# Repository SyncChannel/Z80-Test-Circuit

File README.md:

# Z80-Test-Circuit
https://oshpark.com/projects/BlrcG0fj

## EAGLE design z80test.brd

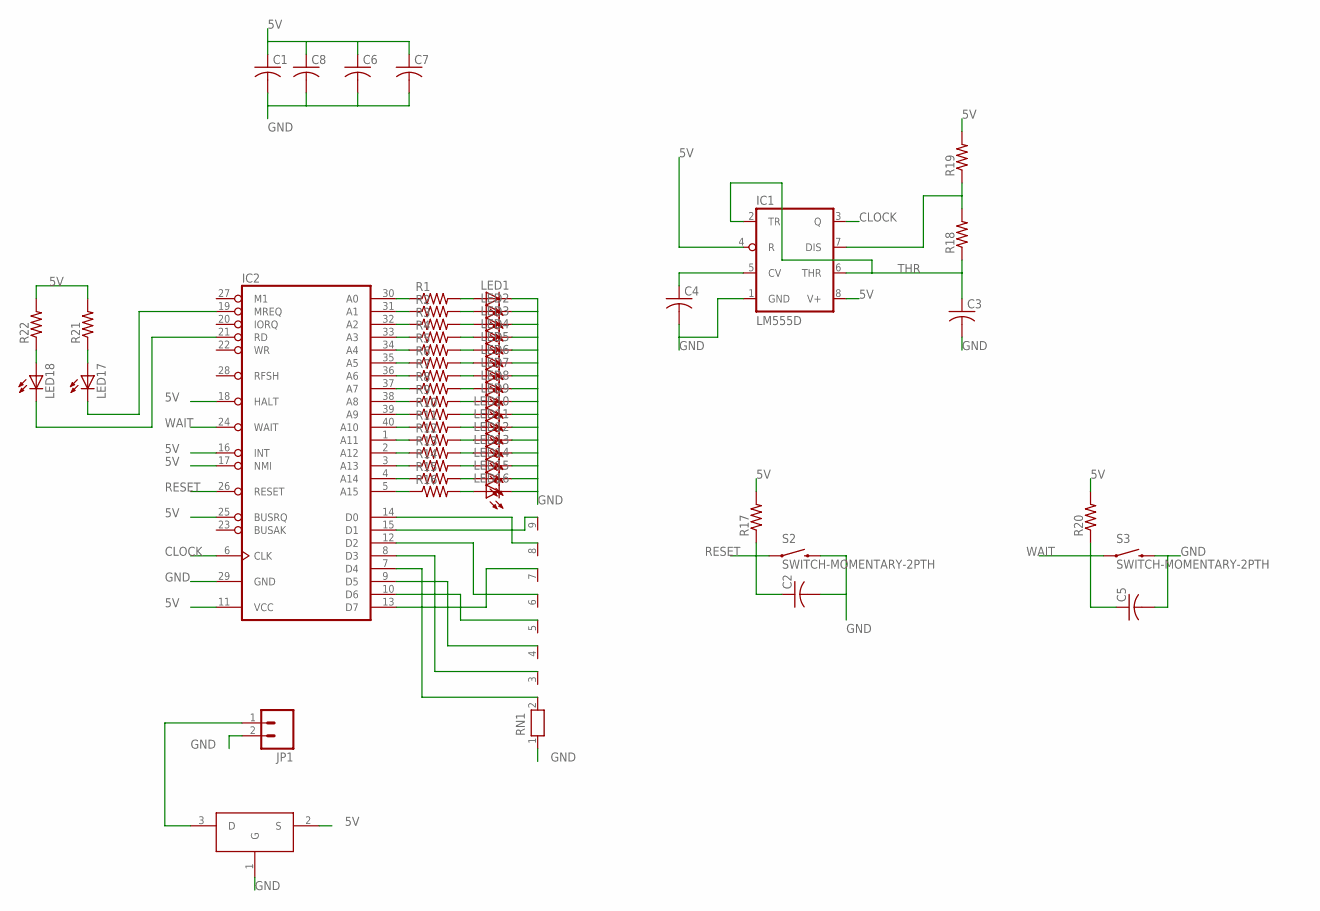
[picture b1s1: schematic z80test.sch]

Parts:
C1: C-USC0805K; C0805K
C2, C3, C4, C5, C6, C7, C8: C-USC0603; C0603
IC1: LM555D; SO08
IC2: Z80CPU; DIL40
JP1: M02PTH; 1X02
LED1, LED2, LED3, LED4, LED5, LED6, LED7, LED8, LED9, LED10, LED11, LED12, LED13, LED14, LED15, LED16, LED17, LED18: LEDCHIPLED_0805; CHIPLED_0805
R1, R2, R3, R4, R5, R6, R7, R8, R9, R10, R11, R12, R13, R14, R15, R16, R17, R18, R19, R20, R21, R22: R-US_R0603; R0603
RN1: RN08; RN-9
S2, S3: SWITCH-MOMENTARY-2PTH; TACTILE-PTH
U$1: PMOS_RP; SOT23-3

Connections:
5V: C1.1, C6.1, C7.1, C8.1, IC1.4 (R), IC1.8 (V+), IC2.11 (VCC), IC2.16 (INT), IC2.17 (NMI), IC2.18 (HALT), IC2.25 (BUSRQ), R17.2, R19.2, R20.2, R21.2, R22.2, U$1.2 (S)
CLOCK: IC1.3 (Q), IC2.6 (CLK)
GND: C1.2, C2.2, C3.2, C4.2, C5.2, C6.2, C7.2, C8.2, IC1.1 (GND), IC2.29 (GND), JP1.2, LED1.C, LED2.C, LED3.C, LED4.C, LED5.C, LED6.C, LED7.C, LED8.C, LED9.C, LED10.C, LED11.C, LED12.C, LED13.C, LED14.C, LED15.C, LED16.C, RN1.1, S2.3 (2), S3.3 (2), U$1.1 (G)
JUNCTION: IC1.7 (DIS), R18.2, R19.1
unnamed: IC2.15 (D1), RN1.9
unnamed: IC2.14 (D0), RN1.8
unnamed: IC2.13 (D7), RN1.7
unnamed: IC2.12 (D2), RN1.6
unnamed: IC2.10 (D6), RN1.5
unnamed: IC2.9 (D5), RN1.4
unnamed: IC2.8 (D3), RN1.3
unnamed: IC2.7 (D4), RN1.2
unnamed: IC2.30 (A0), R1.1
unnamed: IC2.31 (A1), R2.1
unnamed: IC2.32 (A2), R3.1
unnamed: IC2.33 (A3), R4.1
unnamed: IC2.34 (A4), R5.1
unnamed: IC2.35 (A5), R6.1
unnamed: IC2.36 (A6), R7.1
unnamed: IC2.37 (A7), R8.1
unnamed: IC2.38 (A8), R9.1
unnamed: IC2.39 (A9), R10.1
unnamed: IC2.40 (A10), R11.1
unnamed: IC2.1 (A11), R12.1
unnamed: IC2.2 (A12), R13.1
unnamed: IC2.3 (A13), R14.1
unnamed: IC2.4 (A14), R15.1
unnamed: IC2.5 (A15), R16.1
unnamed: LED1.A, R1.2
unnamed: LED2.A, R2.2
unnamed: LED3.A, R3.2
unnamed: LED4.A, R4.2
unnamed: LED5.A, R5.2
unnamed: LED6.A, R6.2
unnamed: LED7.A, R7.2
unnamed: LED8.A, R8.2
unnamed: LED9.A, R9.2
unnamed: LED10.A, R10.2
unnamed: LED11.A, R11.2
unnamed: LED12.A, R12.2
unnamed: LED13.A, R13.2
unnamed: LED14.A, R14.2
unnamed: LED15.A, R15.2
unnamed: LED16.A, R16.2
unnamed: C4.1, IC1.5 (CV)
unnamed: JP1.1, U$1.3 (D)
unnamed: LED17.A, R21.1
unnamed: LED18.A, R22.1
unnamed: IC2.19 (MREQ), LED17.C
unnamed: IC2.21 (RD), LED18.C
RESET: C2.1, IC2.26 (RESET), R17.1, S2.1
THR: C3.1, IC1.2 (TR), IC1.6 (THR), R18.1
WAIT: C5.1, IC2.24 (WAIT), R20.1, S3.1

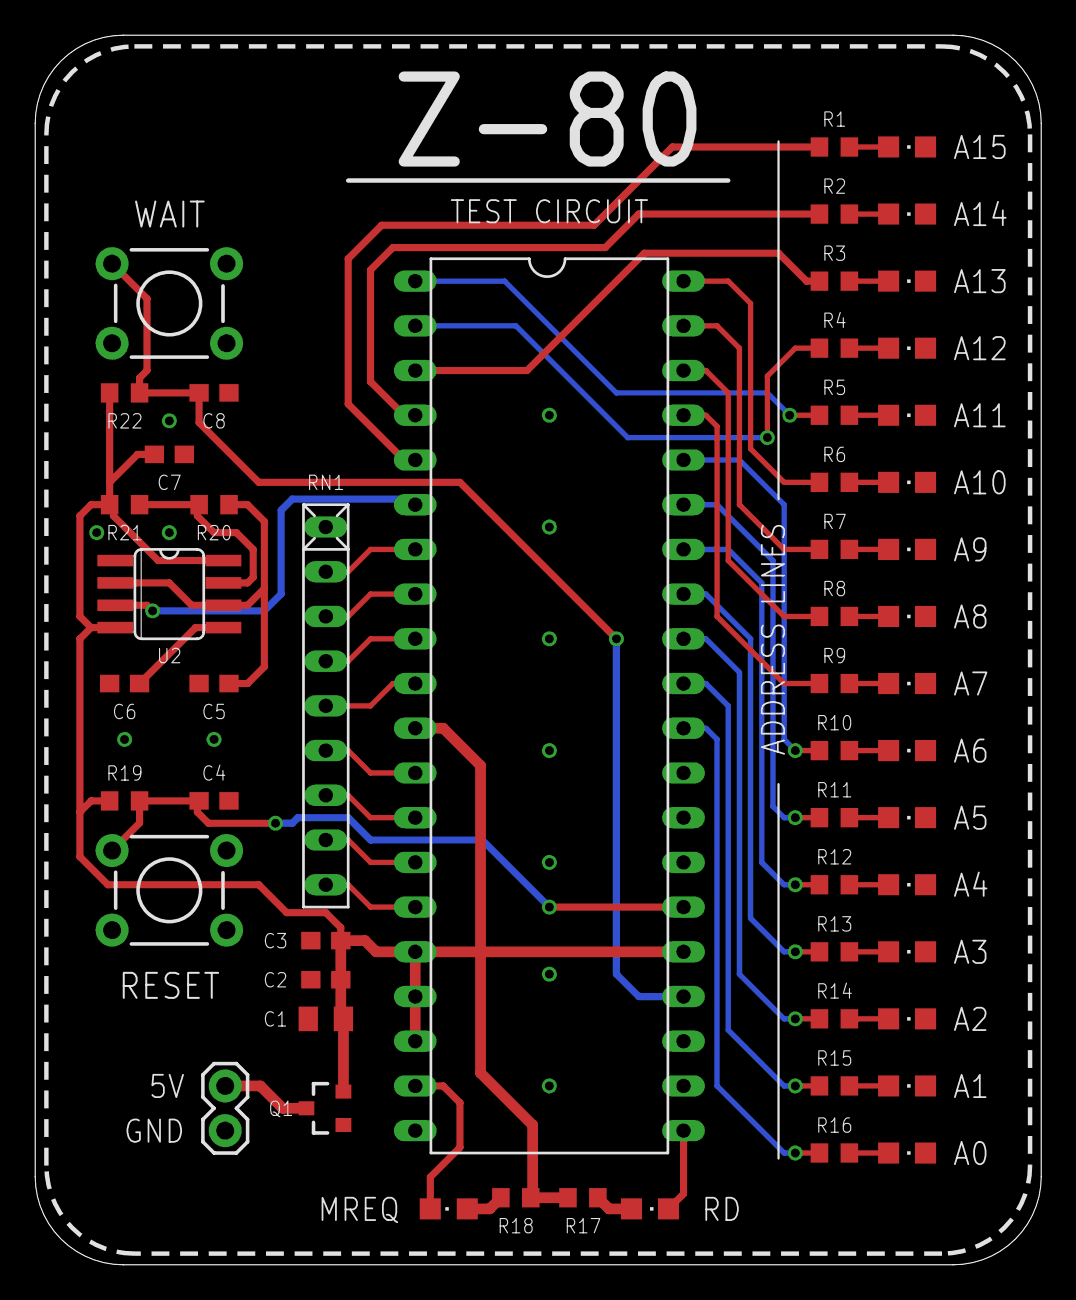
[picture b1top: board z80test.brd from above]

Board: 2 copper layers, 57.1 x 69.8 mm, 55 parts (0 on the bottom side), 53 nets.

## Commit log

2017-09-23 Update LICENSE

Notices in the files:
parts and their libraries:
SparkFun-Electromechanical: Licensing: Creative Commons ShareAlike 4.0 International - https://creativecommons.org/licenses/by-sa/4.0
